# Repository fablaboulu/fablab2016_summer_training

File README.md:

#Project summary
This repo contains the results of a two-week summer training (06.06.2016 - 17.06.2016) of a group of 14 high-schoolers and secondary school students (15 -18 years) at **[FabLab Oulu](http://www.oulu.fi/fablab/) (University of Oulu, Finland)**. This activity was part of the [Fablab4School project](http://fablab4school.fi). 

During the training participants familiarised with FabLab concept, machines and tools. They learnt how to create a Arduino Shield from scratch, including several sensors and actuators, how to use a 3D printer and a laser cutter to create the mechanics for an electronic device as well as Arduino programming principles. The training followed a practical approach. Trainees created a robot that meets the requirements provided during the first day. 

The trainees were divided in 4 teams. They had to implement an alarm-bot which is able to move, make noise and turn-on/off the lights. The only way of stopping the robot is catching it up and shake it. Each team implemented a different robot: 
* An owl
* A frog
* A foot
* A UFO 

More information in the [summer training blog](https://fablaboulusummertraining.wordpress.com/) 

This summer training program is possible thanks to the financial support of **City of Oulu**, **FabLab Oulu**, and the  **Faculty of Information Technology and Electrical Engineering (University of Oulu) through the project FabLab4School**.

#Project structure
There is one folder per team. Each folder includes:
 * Eagle files for the arduino shield
 * 2D/3D models for the mechanics
 * Arduino source code

In addition there is one folder named instructor in which I have placed the Arduino code that was created by the instructor as a guideline. 

#Software utilized:
We utilized the following software:
##2D/3D models
* Inkscape (.svg)
* Freecad (.FCStd1, .stl)
* Autodesk 123d (.123dx)
* MeshMixer (.mix)
## Schematics
* Eagle(.brd, .sch)

##Coding
* Arduino (.ino)

#License

## Arduino code
All the code is distributed as free software: you can redistribute it and/or modify it under the terms of the GNU General Public License as published by the Free Software Foundation, either version 3 of the License, or(at your option) any later version. See [http://www.gnu.org/licenses/](http://www.gnu.org/licenses/)

## 2D and 3D Models / Schematics
The 2D and and 3D models as well as the board schematics (Eagle files) are distributed under a [CC Attribution 4.0 International](https://creativecommons.org/licenses/by/4.0/legalcode). Hence you are free to share(copy and redistribute the material in any medium or format)
and adapt (remix, transform, and build upon the material) for any purpose, even commercially under the following terms: (1) Attribution: You must give appropriate credit, provide a link to the license, and indicate if changes were made. You may do so in any reasonable manner, but not in any way that suggests the licensor endorses you or your use.

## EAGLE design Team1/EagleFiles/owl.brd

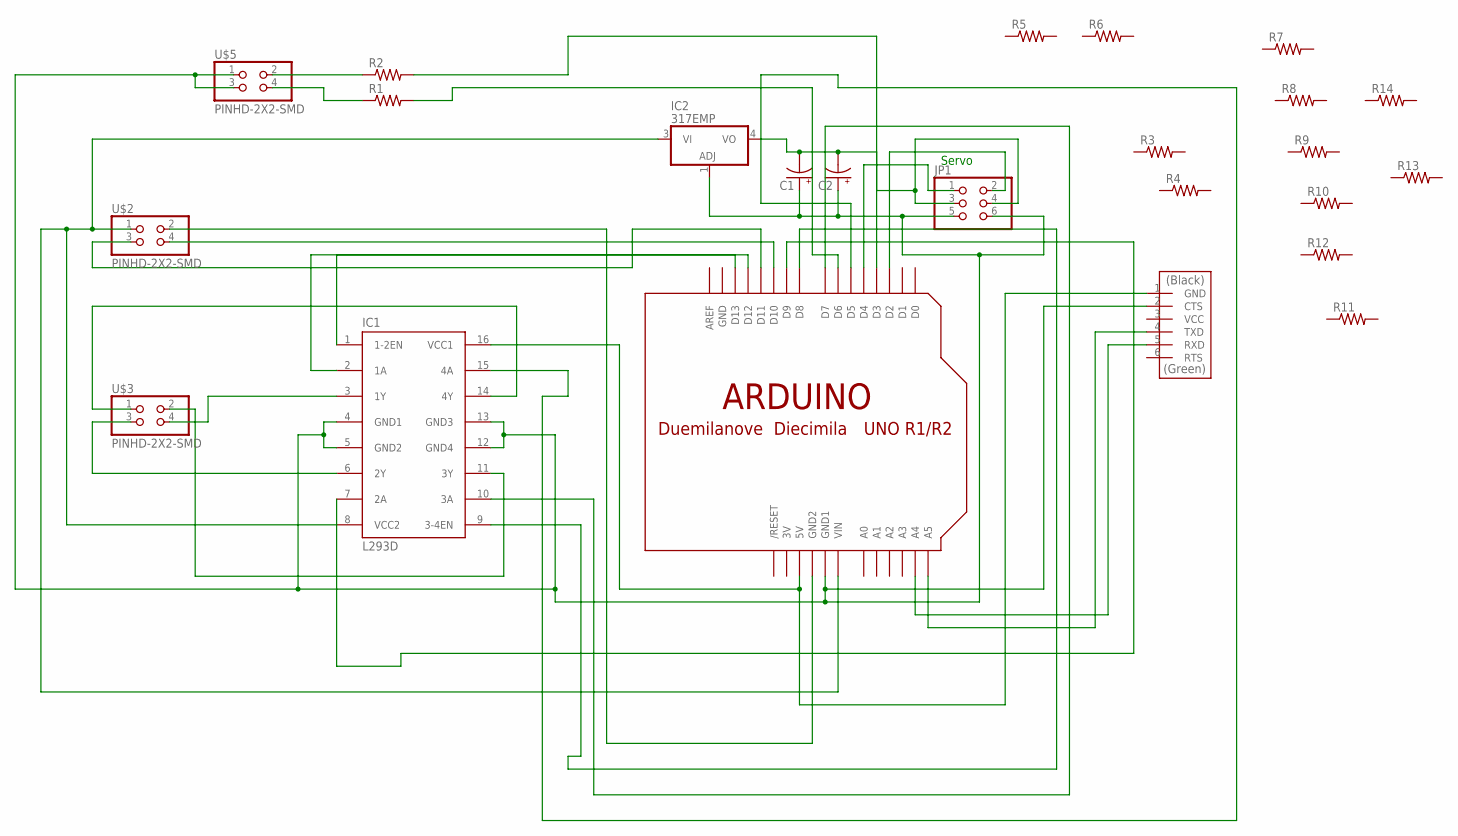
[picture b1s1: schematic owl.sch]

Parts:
C1, C2: CPOL-US085CS-1AR; 085CS_1AR
IC1: L293D; DIL16
IC2: 317EMP; SOT223
JP1: PINHD-2X3-SMD; 2X03SMD
R1, R2, R3, R4, R5, R6, R7, R8, R9, R10, R11, R12, R13, R14: RES-US1206FAB; R1206FAB
U$1: ARDUINO-NOHOLE
U$2, U$3, U$5: PINHD-2X2-SMD; 2X02SMD
U$4: FTDI-SMD-HEADER; 1X06SMD

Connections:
3V: U$1.3V
GND: U$1.GND
unnamed: IC1.6 (2Y), U$3.3
unnamed: IC1.3 (1Y), U$3.4
unnamed: R2.2, U$1.D3
unnamed: IC1.1 (1-2EN), U$1.D13
unnamed: R2.1, U$5.2
unnamed: C1.-, C2.-, IC2.4 (VO), JP1.3, JP1.4
unnamed: U$1.GND2, U$2.2
unnamed: IC1.2 (1A), U$1.D12
unnamed: U$1.D10, U$2.4
unnamed: U$1.D11, U$2.3
unnamed: IC1.16 (VCC1), U$1.5V, U$4.1 (GND)
unnamed: IC1.7 (2A), U$1.D9
unnamed: IC1.9 (3-4EN), U$1.D8
unnamed: IC1.10 (3A), U$1.D7
unnamed: IC1.15 (4A), U$1.D5
unnamed: U$1.A5, U$4.4 (TXD)
unnamed: U$1.A4, U$4.5 (RXD)
unnamed: JP1.2, U$1.D2
unnamed: R1.1, U$5.4
unnamed: R1.2, U$1.D6
unnamed: JP1.1, U$1.D4
unnamed: IC1.14 (4Y), U$3.1
unnamed: IC1.11 (3Y), U$3.2
unnamed: C1.+, C2.+, IC1.4 (GND1), IC1.5 (GND2), IC1.12 (GND4), IC1.13 (GND3), IC2.1 (ADJ), JP1.5, JP1.6, U$1.GND1, U$4.2 (CTS), U$5.1, U$5.3
unnamed: IC1.8 (VCC2), IC2.3 (VI), U$1.VIN, U$2.1

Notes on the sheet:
Servo

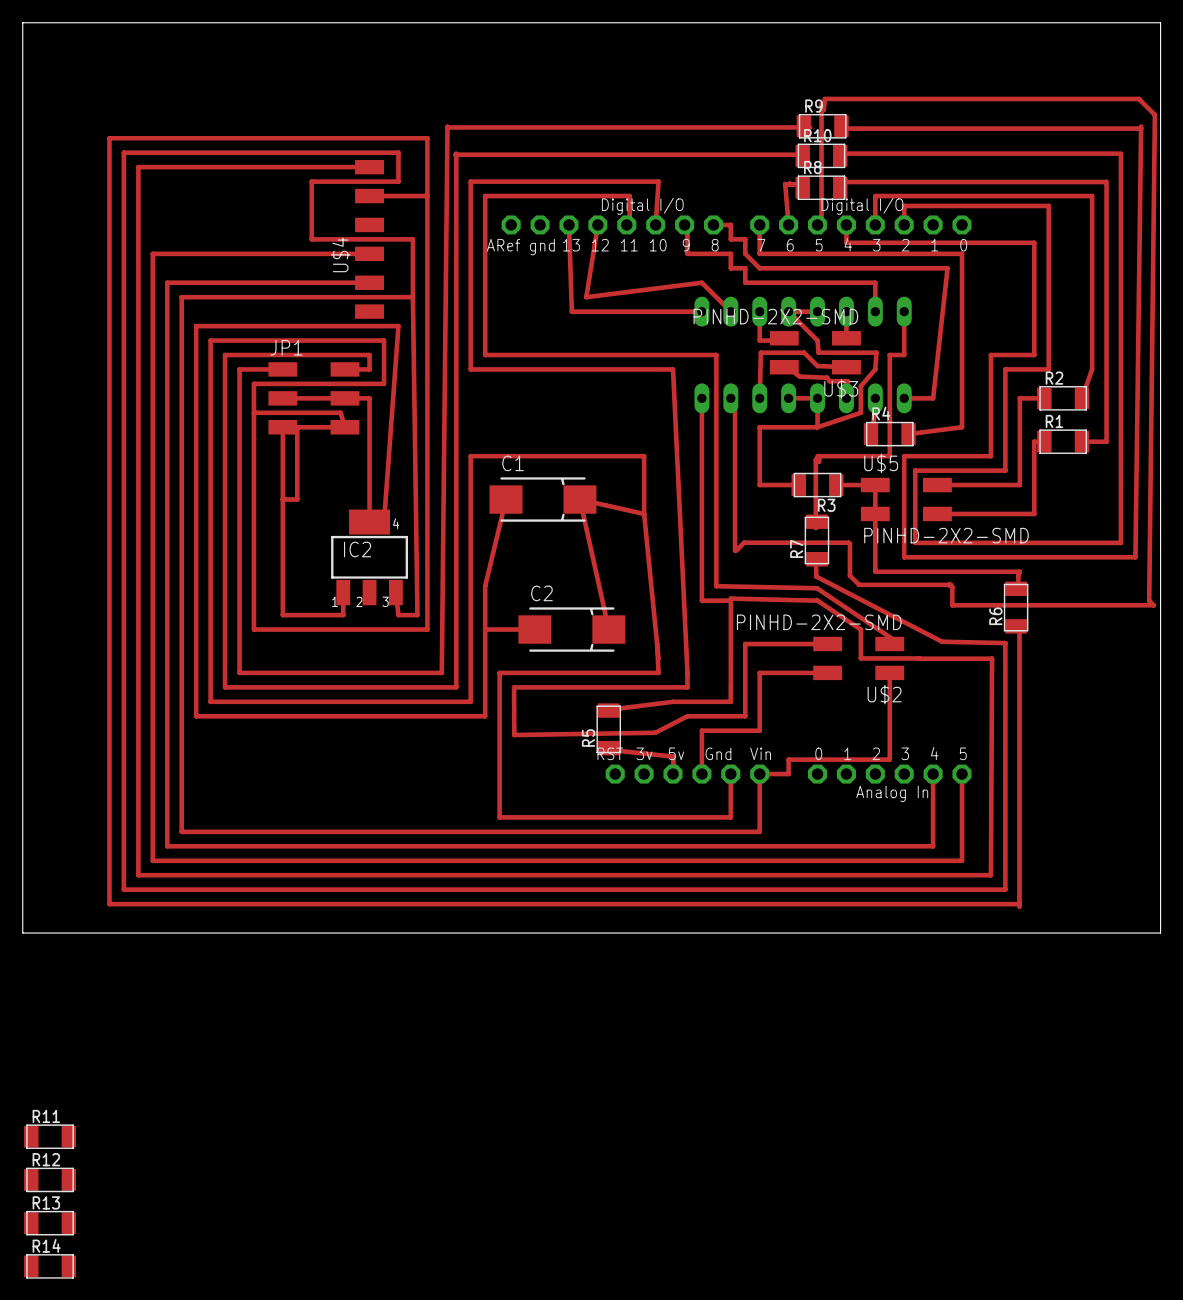
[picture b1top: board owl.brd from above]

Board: 2 copper layers, 100.0 x 80.0 mm, 24 parts (1 on the bottom side), 25 nets.

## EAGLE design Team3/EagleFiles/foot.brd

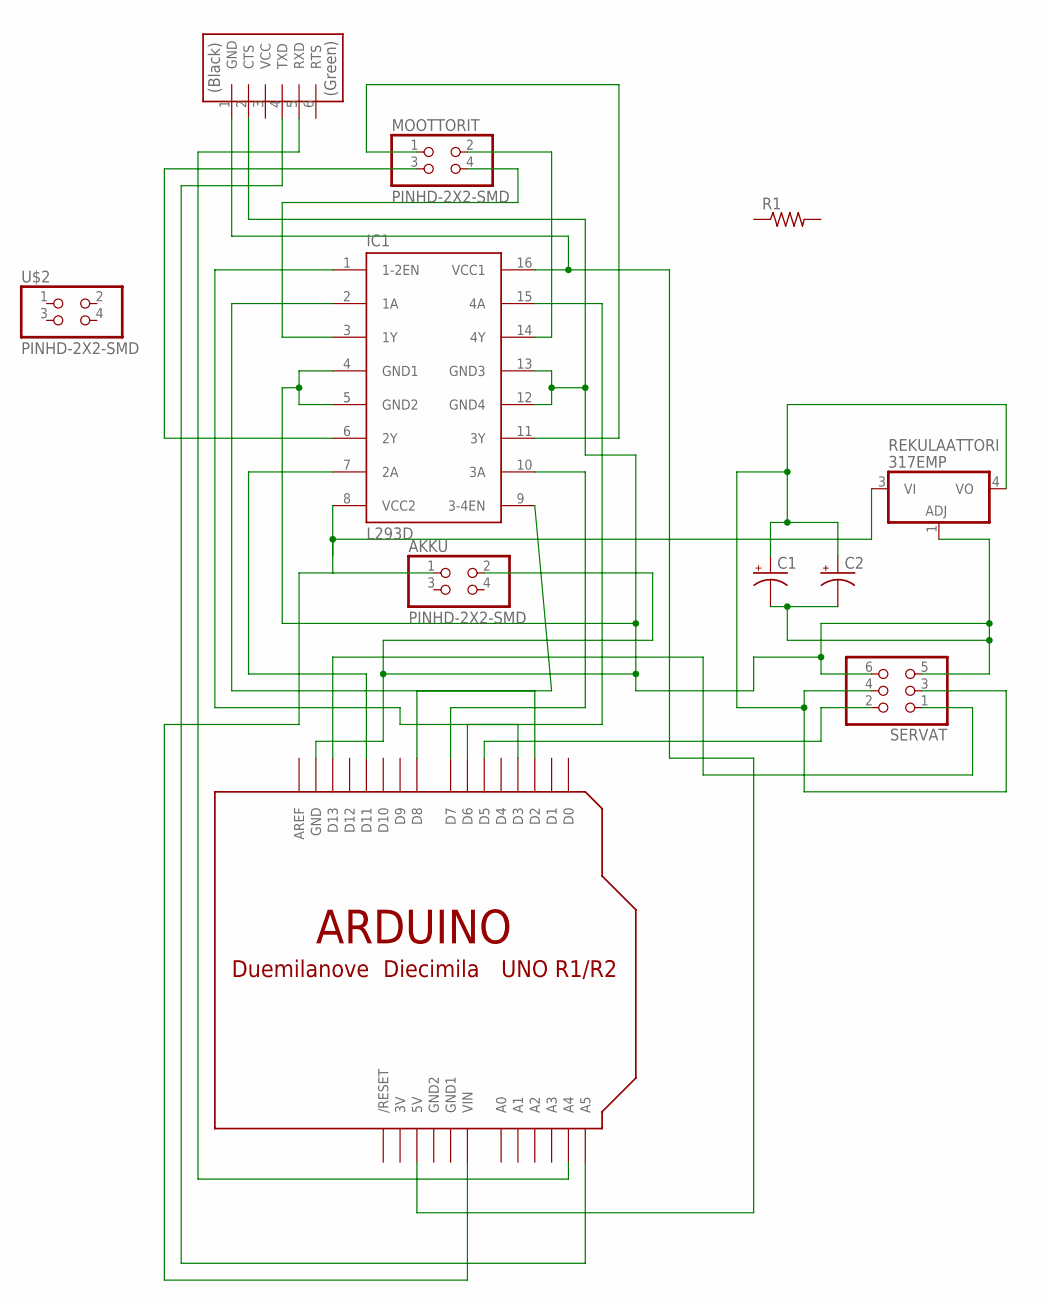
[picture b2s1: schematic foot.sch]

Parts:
AKKU: PINHD-2X2-SMD; 2X02SMD
C1, C2: CPOL-USE/7260-38W; E/7260-38W
IC1: L293D; DIL16
MOOTTORIT: PINHD-2X2-SMD; 2X02SMD
R1: RES-US1206FAB; R1206FAB
REKULAATTORI: 317EMP; SOT223
SERVAT: PINHD-2X3-SMD; 2X03SMD
U$1: ARDUINO-BPLACE
U$2: PINHD-2X2-SMD; 2X02SMD
U$4: FTDI-SMD-HEADER; 1X06SMD

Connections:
3V: U$1.3V
GND1: U$1.GND1
GND2: U$1.GND2
unnamed: SERVAT.1, U$1.D13
unnamed: IC1.10 (3A), U$1.D7
unnamed: IC1.15 (4A), U$1.D6
unnamed: AKKU.1, IC1.8 (VCC2), REKULAATTORI.3 (VI), U$1.VIN
unnamed: IC1.14 (4Y), MOOTTORIT.2
unnamed: IC1.11 (3Y), MOOTTORIT.1
unnamed: IC1.6 (2Y), MOOTTORIT.3
unnamed: AKKU.2, C1.-, C2.-, IC1.4 (GND1), IC1.5 (GND2), IC1.12 (GND4), IC1.13 (GND3), REKULAATTORI.1 (ADJ), SERVAT.5, SERVAT.6, U$1.GND, U$4.2 (CTS)
unnamed: SERVAT.2, U$1.D5
unnamed: IC1.1 (1-2EN), U$1.D3
unnamed: IC1.2 (1A), U$1.D2
unnamed: IC1.7 (2A), U$1.D11
unnamed: U$1.A5, U$4.4 (TXD)
unnamed: U$1.A4, U$4.5 (RXD)
unnamed: C1.+, C2.+, REKULAATTORI.4 (VO), SERVAT.3, SERVAT.4
unnamed: IC1.9 (3-4EN), U$1.D8
unnamed: IC1.3 (1Y), MOOTTORIT.4
unnamed: IC1.16 (VCC1), U$1.5V, U$4.1 (GND)

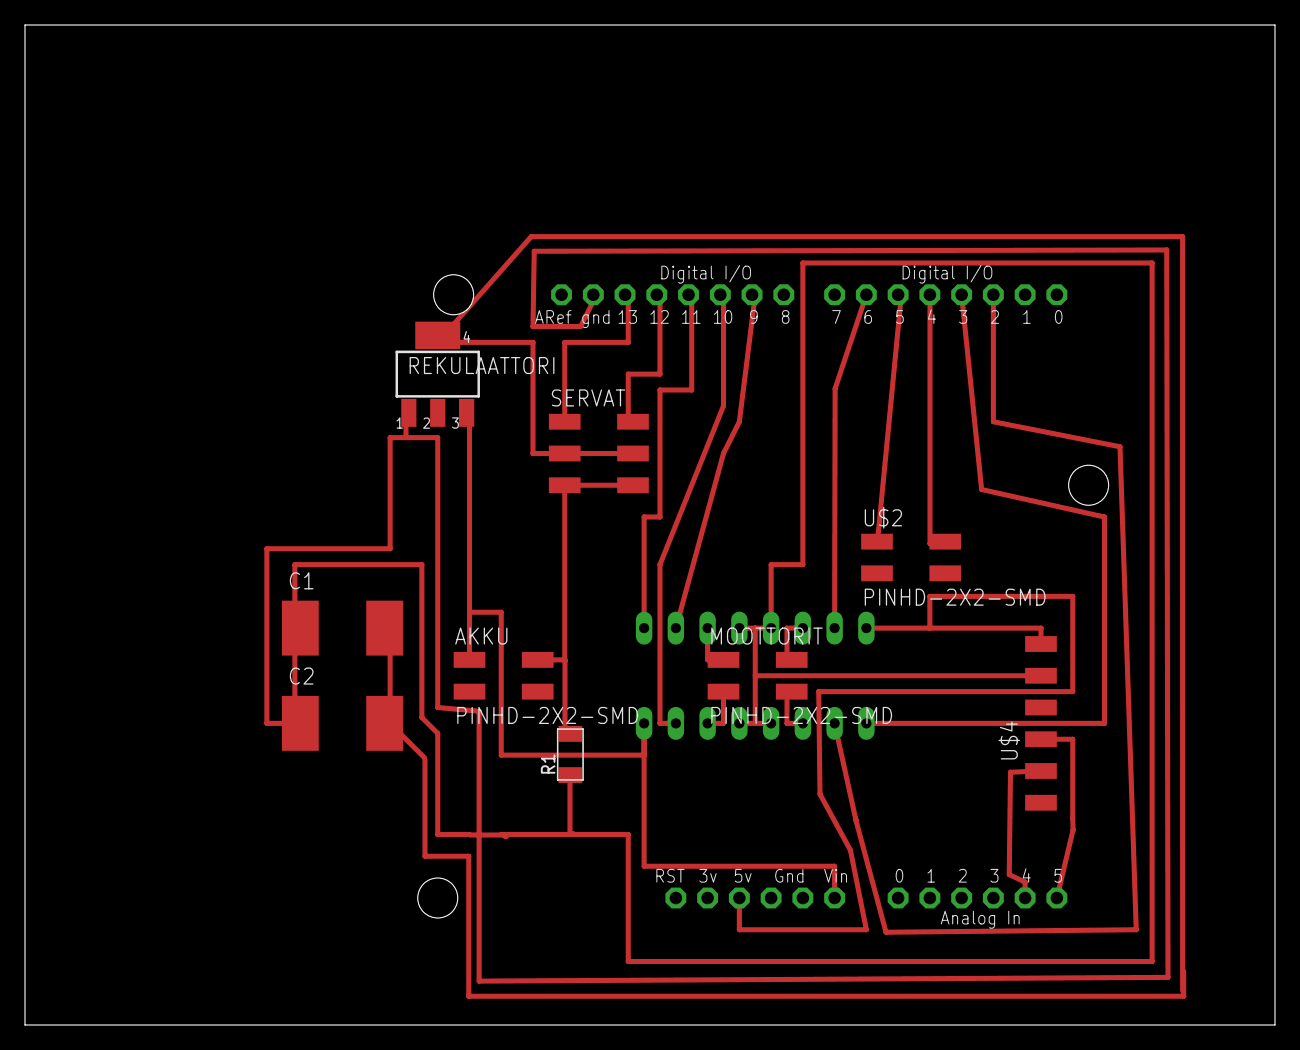
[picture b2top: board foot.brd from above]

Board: 2 copper layers, 100.0 x 80.0 mm, 11 parts (1 on the bottom side), 18 nets.

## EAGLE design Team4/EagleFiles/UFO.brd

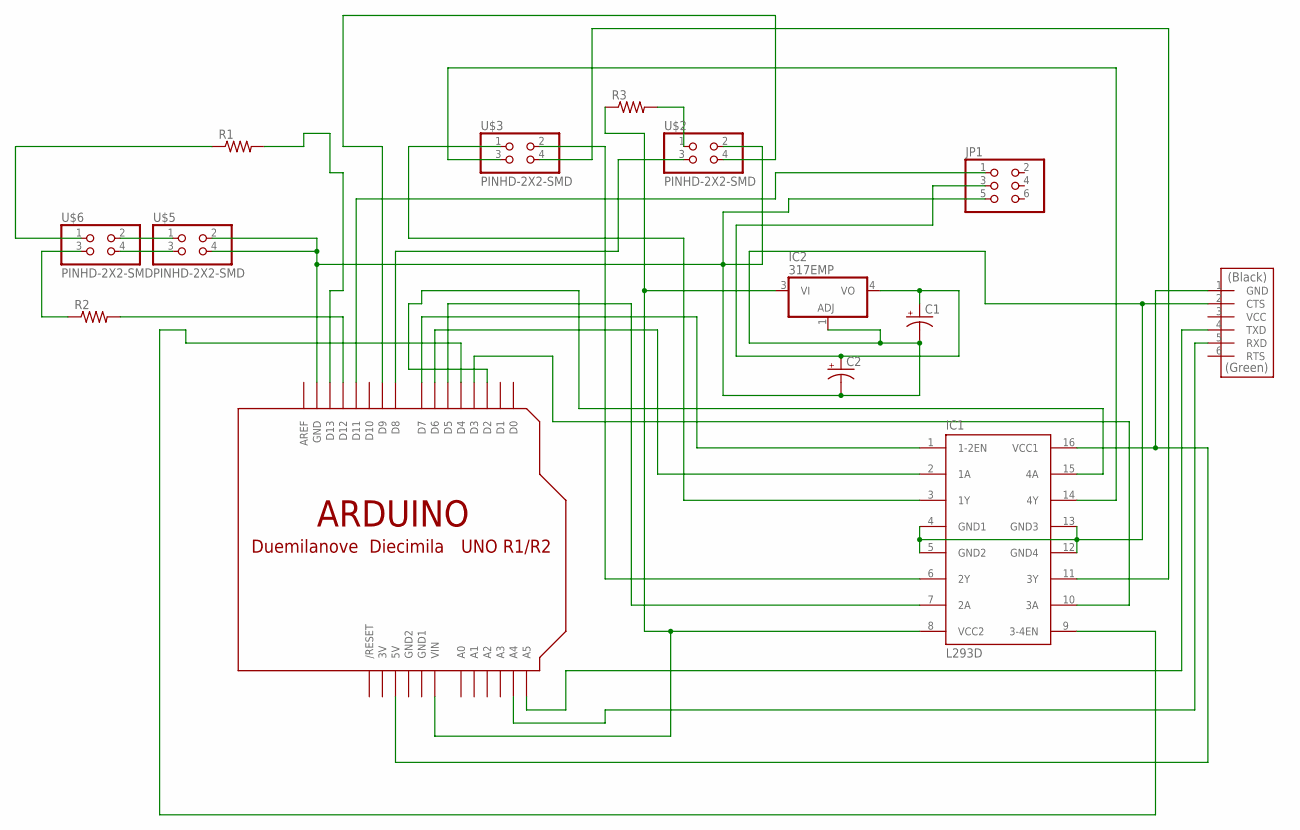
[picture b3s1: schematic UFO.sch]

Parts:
C1, C2: CPOL-USE/7260-38W; E/7260-38W
IC1: L293D; DIL16
IC2: 317EMP; SOT223
JP1: PINHD-2X3-SMD; 2X03SMD
R1, R2: RES-US1206; R1206
R3: RES-US1206FAB; R1206FAB
U$1: ARDUINO-NOHOLE
U$2, U$3, U$5, U$6: PINHD-2X2-SMD; 2X02SMD
U$4: FTDI-SMD-HEADER; 1X06SMD

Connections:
3V: U$1.3V
GND1: U$1.GND1
GND2: U$1.GND2
unnamed: R3.2, U$2.1
unnamed: IC1.1 (1-2EN), U$1.D7
unnamed: IC1.2 (1A), U$1.D6
unnamed: IC1.7 (2A), U$1.D5
unnamed: IC1.15 (4A), U$1.D2
unnamed: IC1.10 (3A), U$1.D3
unnamed: IC1.9 (3-4EN), U$1.D4
unnamed: IC1.3 (1Y), U$3.1
unnamed: IC1.6 (2Y), U$3.2
unnamed: IC1.14 (4Y), U$3.3
unnamed: IC1.11 (3Y), U$3.4
unnamed: IC1.8 (VCC2), IC2.3 (VI), R3.1, U$1.VIN
unnamed: IC1.16 (VCC1), U$1.5V, U$4.1 (GND)
unnamed: R1.2, U$1.D13
unnamed: C1.-, C2.-, IC1.4 (GND1), IC1.5 (GND2), IC1.12 (GND4), IC1.13 (GND3), IC2.1 (ADJ), JP1.5, U$1.GND, U$2.2, U$4.2 (CTS), U$5.2, U$5.4
unnamed: U$5.3, U$6.4
unnamed: U$1.A5, U$4.4 (TXD)
unnamed: U$1.A4, U$4.5 (RXD)
unnamed: U$5.1, U$6.2
unnamed: U$1.D8, U$2.3
unnamed: U$1.D9, U$2.4
unnamed: R2.2, U$1.D12
unnamed: R2.1, U$6.3
unnamed: R1.1, U$6.1
unnamed: C1.+, C2.+, IC2.4 (VO), JP1.3
unnamed: JP1.1, U$1.D11

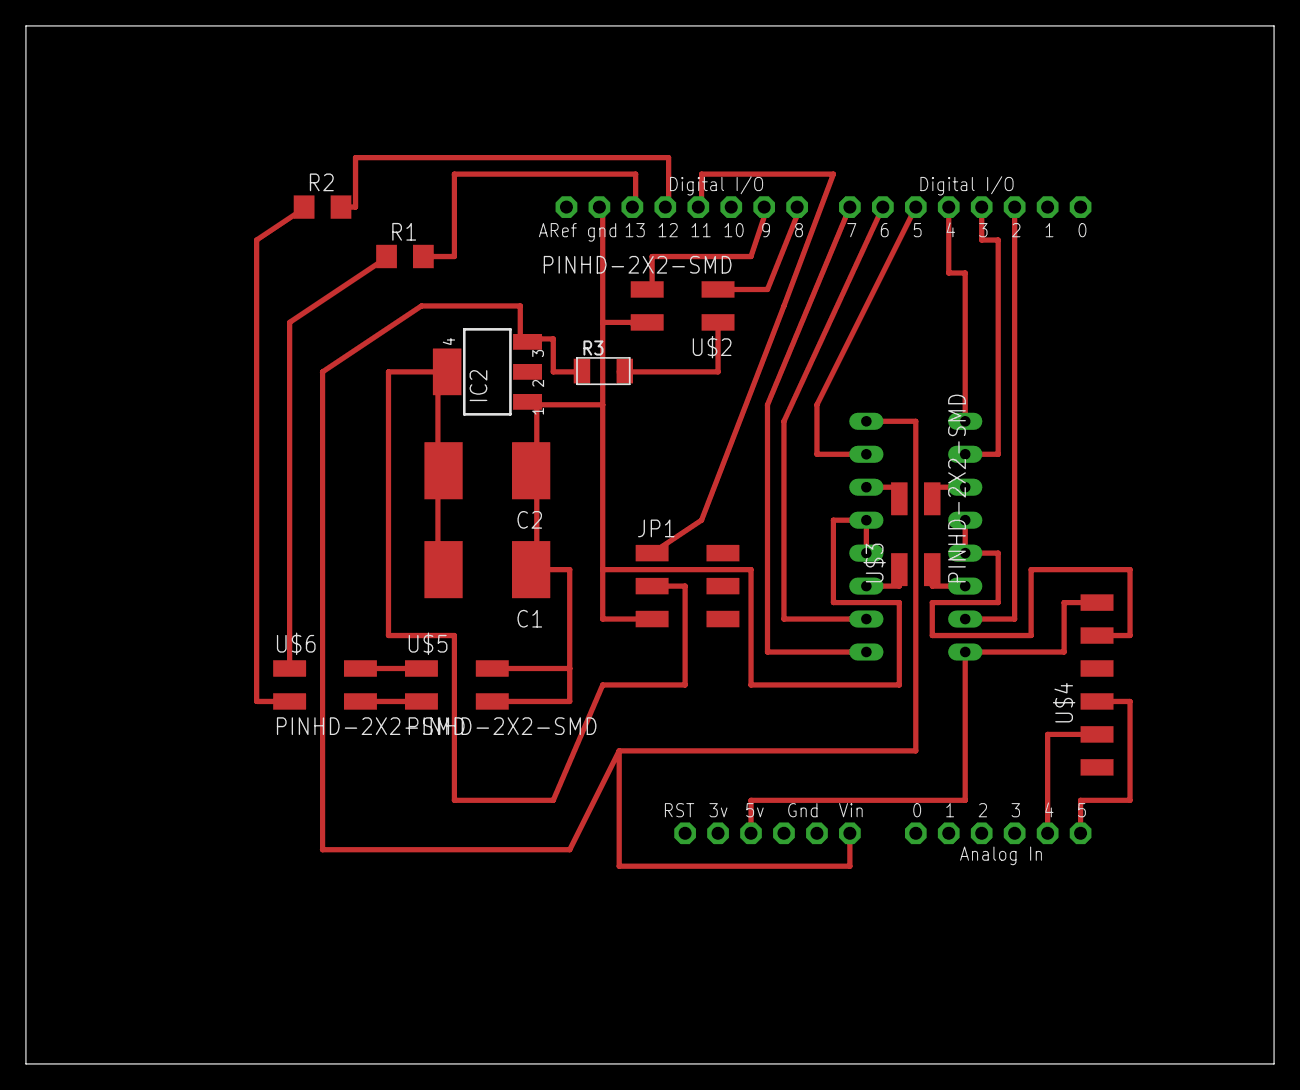
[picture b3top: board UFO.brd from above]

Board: 2 copper layers, 96.2 x 80.0 mm, 14 parts (1 on the bottom side), 26 nets.

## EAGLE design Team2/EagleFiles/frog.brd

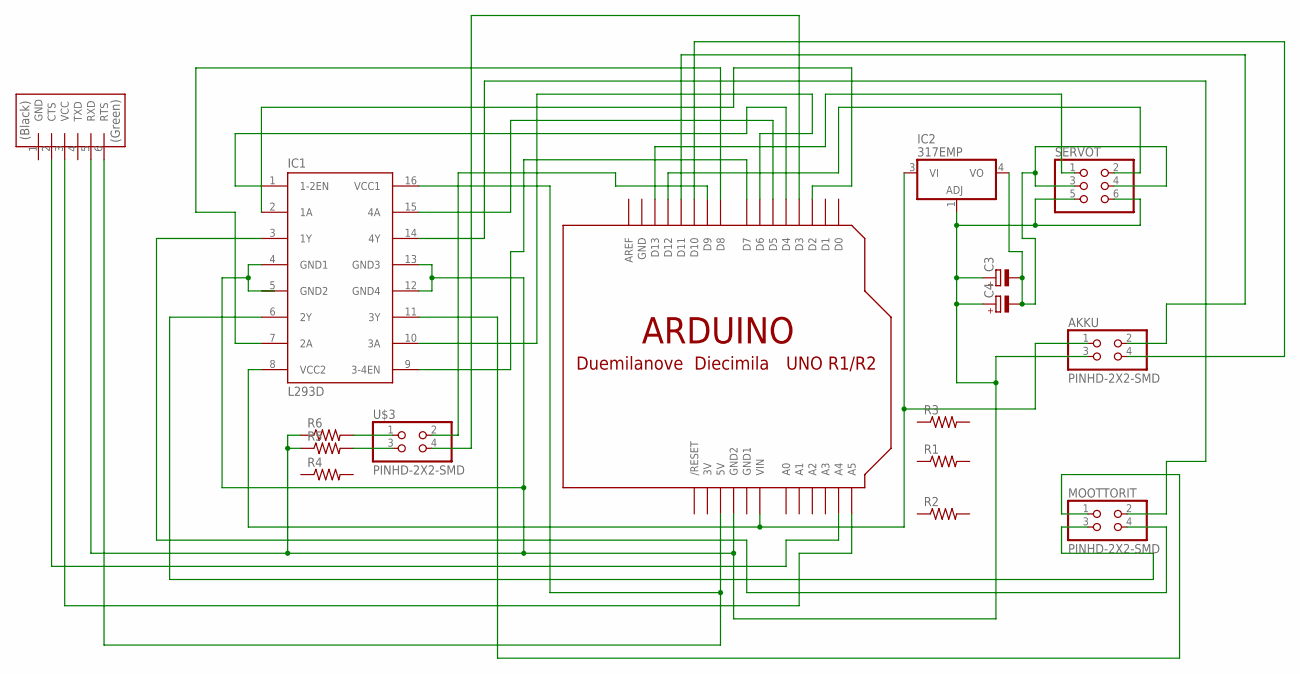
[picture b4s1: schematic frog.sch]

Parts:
AKKU: PINHD-2X2-SMD; 2X02SMD
C3, C4: CPOL-EUE/7260-38W; E/7260-38W
IC1: L293D; DIL16
IC2: 317EMP; SOT223
MOOTTORIT: PINHD-2X2-SMD; 2X02SMD
R1, R2, R3, R4, R5, R6: RES-US1206FAB; R1206FAB
SERVOT: PINHD-2X3-SMD; 2X03SMD
U$1: ARDUINOUNO; ARDUINO
U$2: FTDI-SMD-HEADER; 1X06SMD
U$3: PINHD-2X2-SMD; 2X02SMD

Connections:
3V: U$1.3V
GND: U$1.GND
GND1: U$1.GND1
GND2: IC1.5 (GND2)
unnamed: IC1.1 (1-2EN), U$1.D4
unnamed: IC1.2 (1A), U$1.D2
unnamed: IC1.3 (1Y), MOOTTORIT.4
unnamed: IC1.6 (2Y), MOOTTORIT.3
unnamed: IC1.7 (2A), U$1.D8
unnamed: IC1.14 (4Y), MOOTTORIT.2
unnamed: AKKU.1, IC1.8 (VCC2), IC2.3 (VI), U$1.VIN
unnamed: IC1.16 (VCC1), U$1.5V, U$2.6 (RTS)
unnamed: IC1.15 (4A), U$1.D5
unnamed: IC1.10 (3A), U$1.D6
unnamed: C3.-, C4.-, IC2.4 (VO), SERVOT.3, SERVOT.4
unnamed: IC1.9 (3-4EN), U$1.D7
unnamed: AKKU.4, U$1.D10
unnamed: U$1.A5, U$2.3 (VCC)
unnamed: U$1.A4, U$2.2 (CTS)
unnamed: SERVOT.1, U$1.D13
unnamed: SERVOT.2, U$1.D12
unnamed: AKKU.2, U$1.D11
unnamed: AKKU.3, C3.+, C4.+, IC1.4 (GND1), IC1.12 (GND4), IC1.13 (GND3), IC2.1 (ADJ), R5.1, R6.1, SERVOT.5, SERVOT.6, U$1.GND2, U$2.5 (RXD)
unnamed: IC1.11 (3Y), MOOTTORIT.1
unnamed: R5.2, U$3.3
unnamed: R6.2, U$3.1
unnamed: U$1.D9, U$3.2
unnamed: U$1.D3, U$3.4

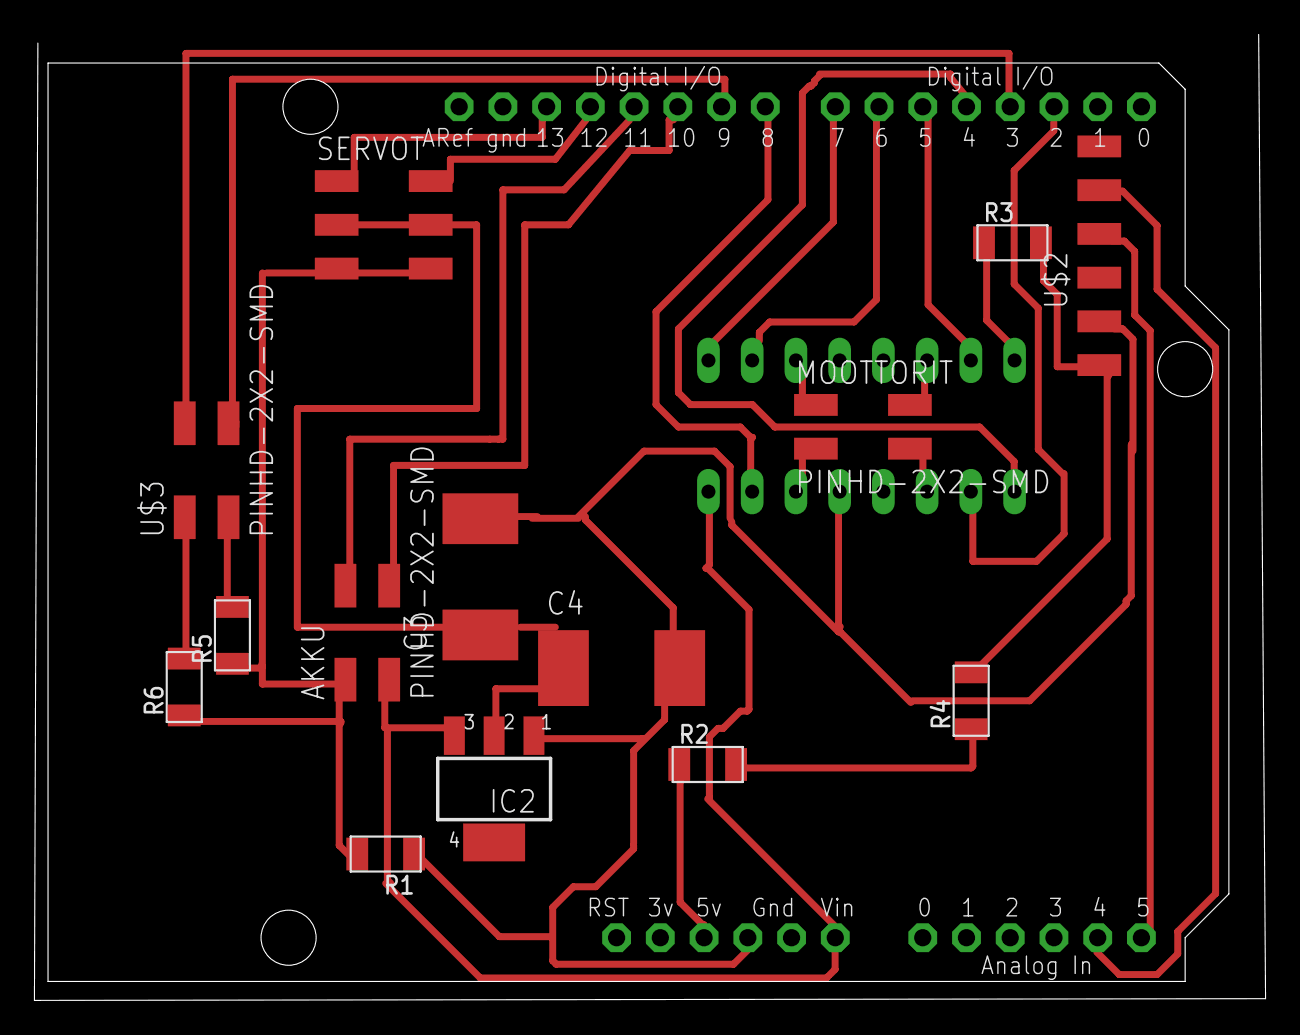
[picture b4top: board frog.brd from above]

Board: 2 copper layers, 71.5 x 56.1 mm, 16 parts (1 on the bottom side), 24 nets.

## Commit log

2016-09-26 Added fablab4aschool link
